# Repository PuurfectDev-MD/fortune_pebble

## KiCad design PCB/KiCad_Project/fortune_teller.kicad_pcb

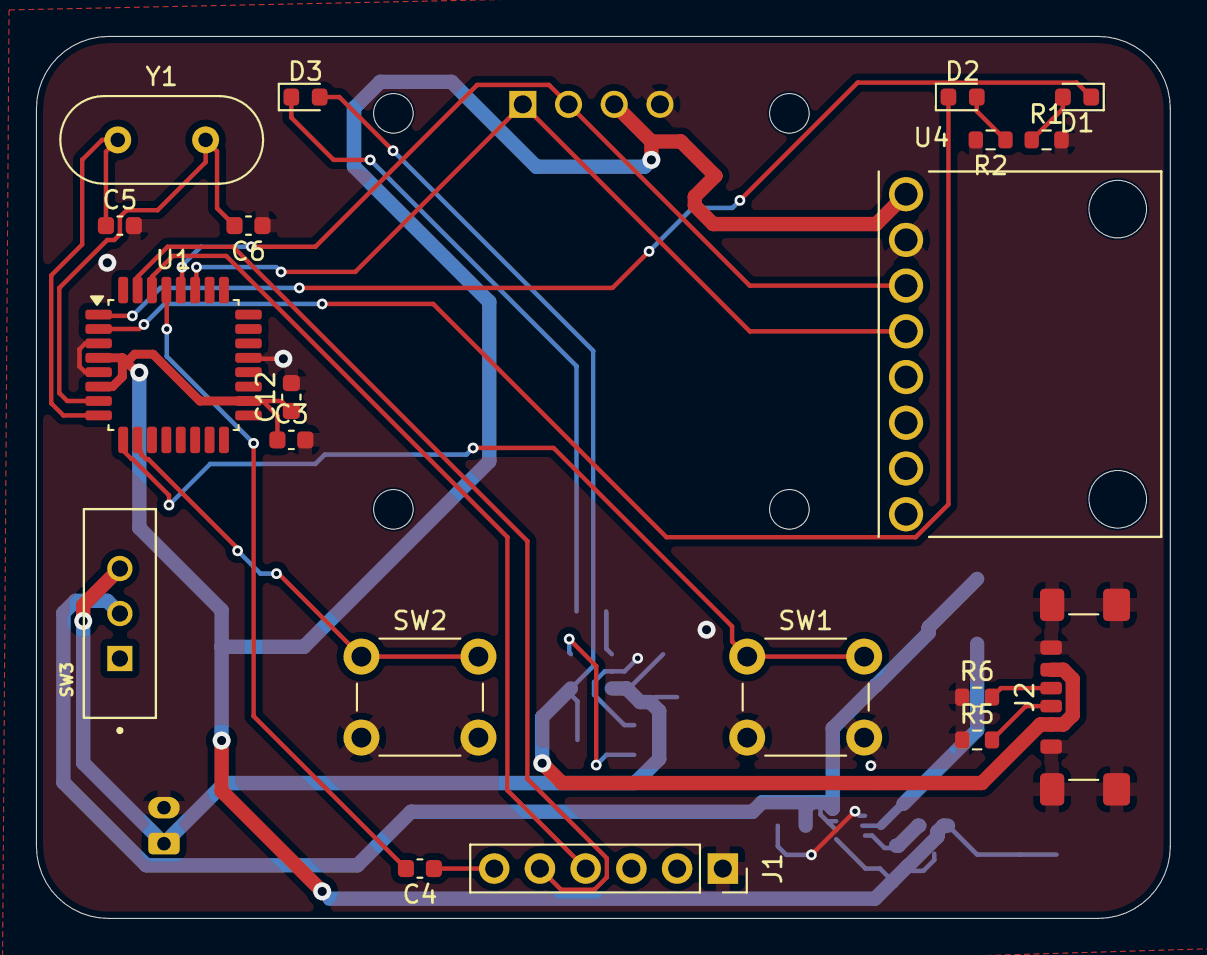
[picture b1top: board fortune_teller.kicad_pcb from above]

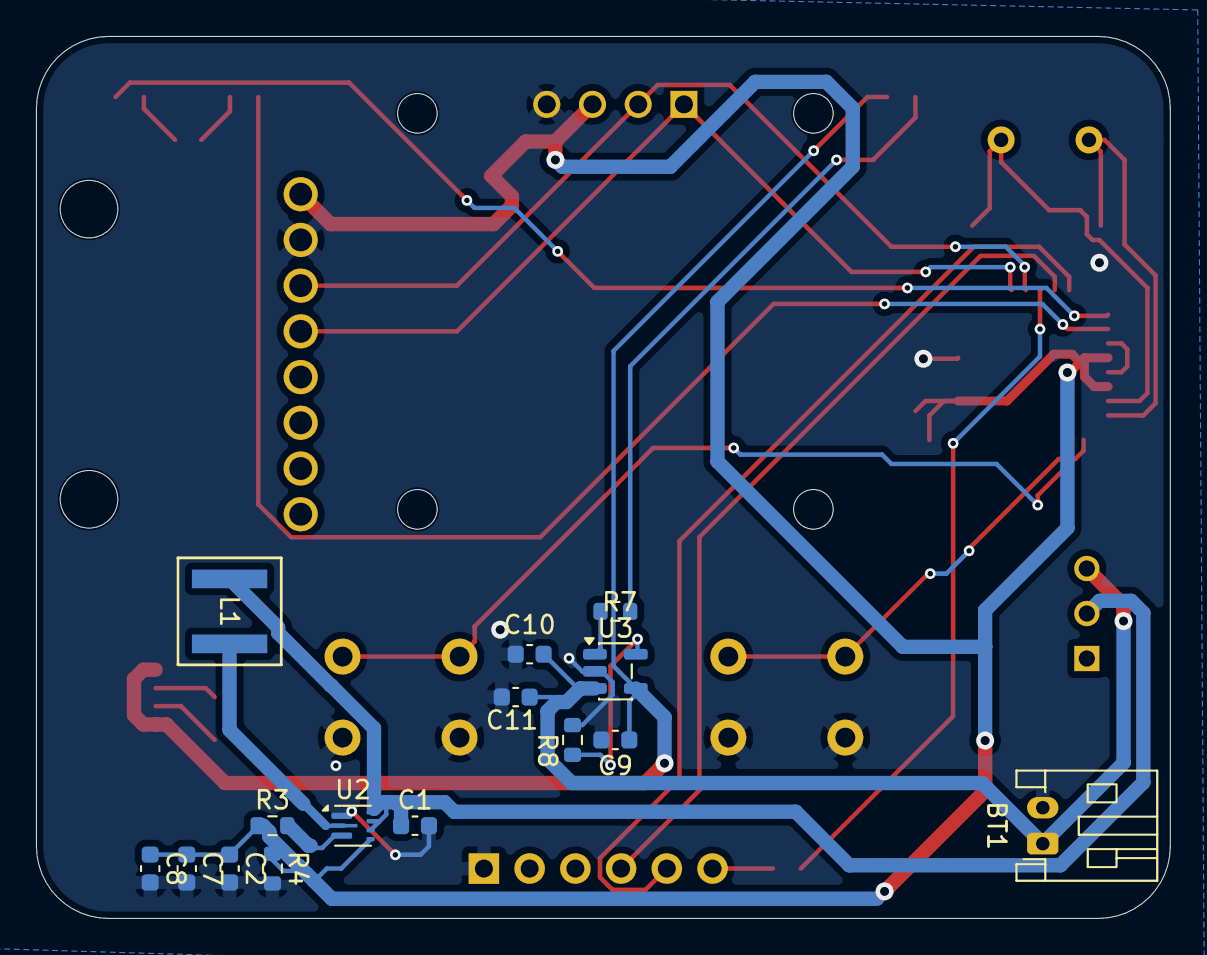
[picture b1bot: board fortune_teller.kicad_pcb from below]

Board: 2 copper layers, 63.0 x 49.0 mm, 36 parts (15 on the bottom side), 26 nets.

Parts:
BT1: Battery_Cell; JST_PH_S2B-PH-K_1x02_P2.00mm_Horizontal
C1, C3: 10uf; C_0603_1608Metric
C2, C7, C8: 22uf; C_0603_1608Metric
C4, C12: 100nf; C_0603_1608Metric
C5, C6: 22pf; C_0603_1608Metric
C9, C10, C11: 4.7uF; C_0603_1608Metric
D1, D2, D3: LED; LED_0603_1608Metric
J1: USB to TTL; PinSocket_1x06_P2.54mm_Vertical
J2: USB_C_Receptacle_PowerOnly_6P; USB_C_Receptacle_GCT_USB4135-GF-A_6P_TopMnt_Horizontal
L1: 1uH; IND_XEL5030_3.1_COC
OL1: OLED; OLED_128x64
R1, R2: 330; R_0603_1608Metric
R3: 732k; R_0603_1608Metric
R4: 100k; R_0603_1608Metric
R5, R6: 5.1k; R_0603_1608Metric
R7: 470; R_0603_1608Metric
R8: 2k; R_0603_1608Metric
SW1, SW2: Switch; SW_PUSH_6mm_H8.5mm
SW3: SW_Push_SPDT; SW_MINI-SPDT-SW
U1: ATmega328P-A; TQFP-32_7x7mm_P0.8mm
U2: TPS61022; Texas_RWU0007A_VQFN-7_2x2mm_P0.5mm
U3: MCP73831-2-OT; SOT-23-5
U4: GY-521; MODULE_GY-521
Y1: Crystal; Crystal_HC49-4H_Vertical

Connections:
5V: C2.1, C3.1, C7.1, C8.1, C12.1, OL1.3 (VCC), R3.1, R4.1, U1.4 (VCC), U1.6 (VCC), U1.18 (AVCC), U2.4 (FB), U4.VCC
BAT+: C1.1, L1.1, SW3.2 (B), U2.5 (EN), U2.6 (MODE), U2.7 (VIN)
Charge+: BT1.1 (+), C10.1, C11.1, SW3.3 (C), U3.3 (V_{BAT})
GND: BT1.2 (-), C1.2, C2.2, C3.2, C5.2, C6.1, C7.2, C8.2, C9.2, C10.2, C11.2, C12.2, J1.GND, J2.A12 (GND), J2.B12 (GND), J2.SH (SHIELD), OL1.4 (GND), R1.2, R2.2, R4.2, R5.1, R6.1, R8.2, SW1.2, SW2.2, U1.3 (GND), U1.5 (GND), U1.21 (GND), U2.1 (GND), U3.2 (V_{SS}), U4.GND
LED1: D1.1 (K), U1.1 (PD3)
LED2: D2.1 (K), U1.2 (PD4)
unnamed: C4.1, J1.DTR
unnamed: D1.2 (A), R1.1
unnamed: D2.2 (A), R2.1
unnamed: D3.1 (K), R7.1
unnamed: J2.A5 (CC1), R5.2
unnamed: J2.B5 (CC2), R6.2
unnamed: C6.2, U1.7 (XTAL1/PB6), Y1.2
unnamed: C5.1, U1.8 (XTAL2/PB7), Y1.1
unnamed: L1.2, U2.2 (SW)
unnamed: R3.2, U2.3 (VOUT)
unnamed: R8.1, U3.5 (PROG)
unnamed: R7.2, U3.1 (STAT)
RESET: C4.2, U1.29 (~RESET/PC6)
RX_USB: J1.RX, U1.31 (PD1)
SCL: OL1.2 (SCL), U1.28 (PC5), U4.SCL
SDA: OL1.1 (SDA), U1.27 (PC4), U4.SDA
SWTCH_1: SW1.1, U1.9 (PD5)
SWTCH_2: SW2.1, U1.10 (PD6)
TX_USB: J1.TX, U1.30 (PD0)
VBUS: C9.1, D3.2 (A), J2.A9 (VBUS), J2.B9 (VBUS), U3.4 (V_{DD})

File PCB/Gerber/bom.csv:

Designator,Footprint,Quantity,Value,LCSC Part #
BT1,JST_PH_S2B-PH-K_1x02_P2.00mm_Horizontal,1,Battery_Cell,
"C1, C3",0603,2,10uf,
"C10, C11, C9",0603,3,4.7uF,
"C12, C4",0603,2,100nf,
"C2, C7, C8",0603,3,22uf,
"C5, C6",0603,2,22pf,
"D1, D2, D3",0603,3,LED,
J1,PinSocket_1x06_P2.54mm_Vertical,1,USB to TTL,
J2,USB_C_Receptacle_GCT_USB4135-GF-A_6P_TopMnt_Horizontal,1,USB_C_Receptacle_PowerOnly_6P,
L1,IND_XEL5030_3.1_COC,1,1uH,
OL1,OLED_128x64,1,OLED,
"R1, R2",0603,2,330,
R3,0603,1,732k,
R4,0603,1,100k,
"R5, R6",0603,2,5.1k,
R7,0603,1,470,
R8,0603,1,2k,
"SW1, SW2",SW_PUSH_6mm_H8.5mm,2,Switch,
SW3,SW_MINI-SPDT-SW,1,SW_Push_SPDT,
U1,TQFP-32_7x7mm_P0.8mm,1,ATmega328P-A,
U2,Texas_RWU0007A_VQFN-7_2x2mm_P0.5mm,1,TPS61022,
U3,SOT-23-5,1,MCP73831-2-OT,
U4,MODULE_GY-521,1,GY-521,
Y1,Crystal_HC49-4H_Vertical,1,Crystal,

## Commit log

2026-05-26 PCB completion
2026-05-27 Added BOM
2026-05-28 Case files - STL and f3d
2026-05-29 Zine
